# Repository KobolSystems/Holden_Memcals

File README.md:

# Holden Memcals

## **Project**: Drop-in Replacement Memcals for Delco '808 ECUs 

<!-- Repo Cover Image -->

<!-- Repo Stats -->

## Details
<p align="justify"> 
Holden Memcals is a repository dedicated to the development of replacement memcals for the VN-VT Commodore ECU. This repository serves as a comprehensive resource, storing all publicly available tunes for these memcals and offering detailed instructions on how to assemble and program existing tunes to them. Whether you are looking to enhance your vehicle's performance or simply maintain its functionality, Holden Memcals provides the necessary tools and information to support your endeavors.
</p>

<!-- To Do List -->
## Project To Do List
- [ ] Reverse engineer memcal
  - [ ] Analyze original memcal architecture
  - [ ] Identify key components and their functions
  - [ ] Document findings

- [ ] Design PCBs
  - [ ] Create schematics
  - [ ] Design PCB layout
  - [ ] Prototype and test PCB
  - [ ] Finalize design

- [ ] Sort tunes
  - [ ] Gather publicly available tunes
  - [ ] Categorize tunes based on vehicle model and specifications
  - [ ] Verify and validate tune files

- [ ] Upload tunes
  - [ ] Organize tunes into appropriate directories
  - [ ] Create metadata files for each tune (e.g., version, date, author)
  - [ ] Ensure tunes are correctly formatted and ready for use

- [ ] Write documentation
  - [ ] Develop detailed assembly instructions
  - [ ] Create programming guides for existing tunes
  - [ ] Write a troubleshooting guide
  - [ ] Document reverse engineering process
  - [ ] Update README with project overview and usage instructions

<!-- Licencing Always at the Bottom -->
## Licencing

This project is licensed under the Creative Commons Attribution-NonCommercial-ShareAlike 4.0 International License.

You are free to:

- **Share** — copy and redistribute the material in any medium or format
- **Adapt** — remix, transform, and build upon the material

Under the following terms:

- **Attribution** — You must give appropriate credit, provide a link to the license, and indicate if changes were made. You may do so in any reasonable manner, but not in any way that suggests the licensor endorses you or your use.
- **NonCommercial** — You may not use the material for commercial purposes.
- **ShareAlike** — If you remix, transform, or build upon the material, you must distribute your contributions under the same license as the original.

No additional restrictions — You may not apply legal terms or technological measures that legally restrict others from doing anything the license permits.

For more information, please visit [Creative Commons Attribution-NonCommercial-ShareAlike 4.0 International License](https://creativecommons.org/licenses/by-nc-sa/4.0/).

## Disclaimer
<p align="justify"> 
The tunes, BIN, ADX, and XDF files included in this repository are written by third parties (including Holden and other enthusiasts). These files may not be suitable for all applications. Kobol Systems makes no guarantee of their fitness for any particular purpose. Use of these files is entirely at your own risk. 
<br><br>
By using these files, you acknowledge that Kobol Systems is not responsible for any damage or issues that may arise from their use. Always ensure that any modifications to your vehicle's ECU are performed by a qualified professional and that you understand the potential risks involved.
</p>

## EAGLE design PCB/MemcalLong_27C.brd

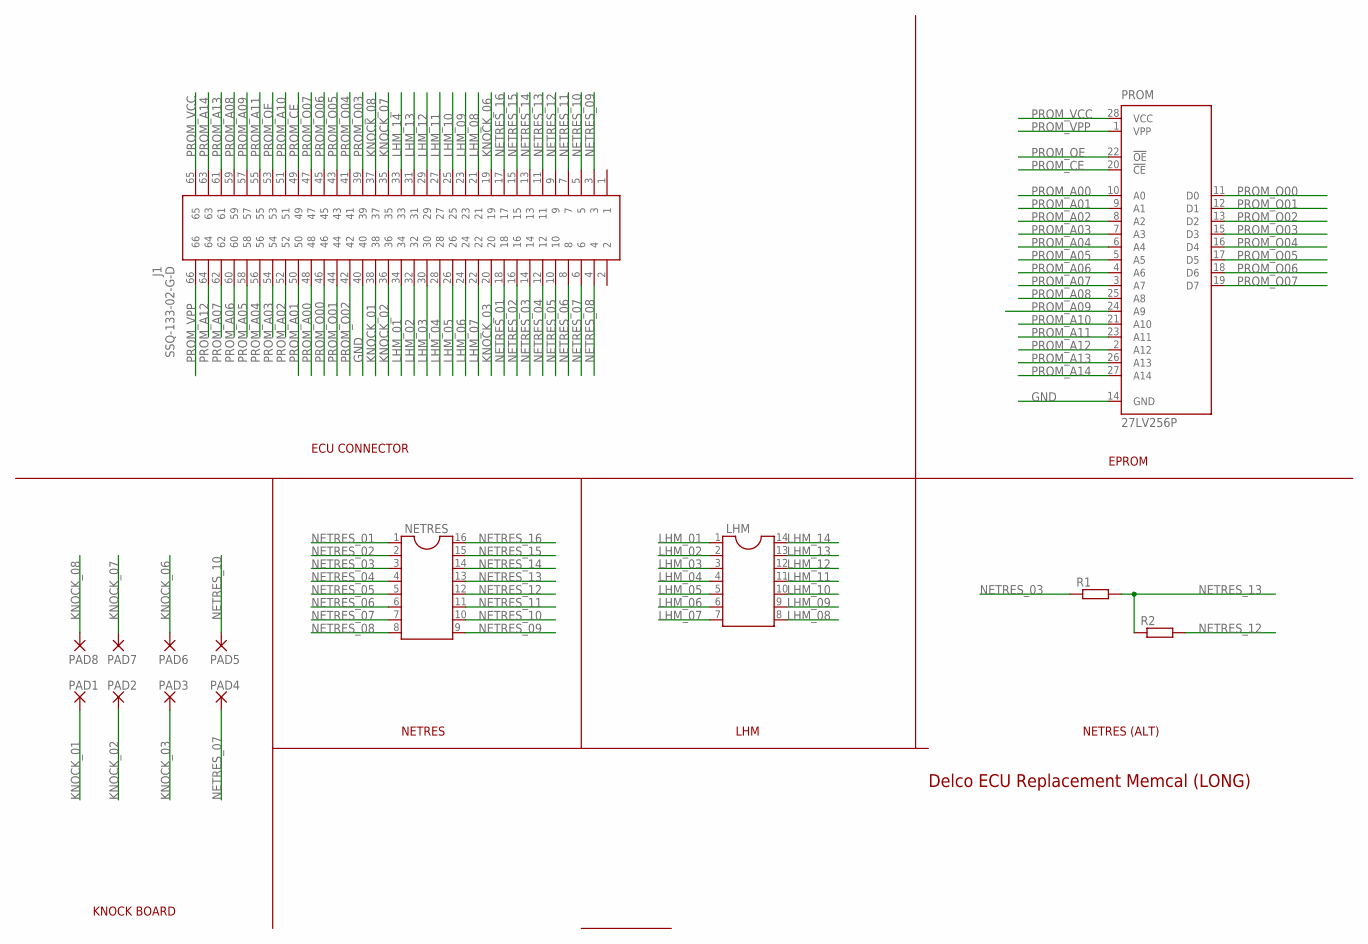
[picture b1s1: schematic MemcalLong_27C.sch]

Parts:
J1: SSQ-133-02-G-D; SSQ-133-XX-YYY
LHM: DIL14S; SOCKET-14
NETRES: DIL16S; SOCKET-16
PAD1, PAD2, PAD3, PAD4, PAD5, PAD6, PAD7, PAD8: SMD2; SMD1,27-2,54
PROM: 27LV256P; DIL28-6
R1, R2: R-EU_0204/7; 0204/7

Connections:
GND: J1.40, PROM.14 (GND)
KNOCK_01: J1.38, PAD1.1
KNOCK_02: J1.36, PAD2.1
KNOCK_03: J1.20, PAD3.1
KNOCK_06: J1.19, PAD6.1
KNOCK_07: J1.35, PAD7.1
KNOCK_08: J1.37, PAD8.1
LHM_01: J1.34, LHM.1
LHM_02: J1.32, LHM.2
LHM_03: J1.30, LHM.3
LHM_04: J1.28, LHM.4
LHM_05: J1.26, LHM.5
LHM_06: J1.24, LHM.6
LHM_07: J1.22, LHM.7
LHM_08: J1.21, LHM.8
LHM_09: J1.23, LHM.9
LHM_10: J1.25, LHM.10
LHM_11: J1.27, LHM.11
LHM_12: J1.29, LHM.12
LHM_13: J1.31, LHM.13
LHM_14: J1.33, LHM.14
NETRES_01: J1.18, NETRES.1
NETRES_02: J1.16, NETRES.2
NETRES_03: J1.14, NETRES.3, R1.1
NETRES_04: J1.12, NETRES.4
NETRES_05: J1.10, NETRES.5
NETRES_06: J1.8, NETRES.6
NETRES_07: J1.6, NETRES.7, PAD4.1
NETRES_08: J1.4, NETRES.8
NETRES_09: J1.3, NETRES.9
NETRES_10: J1.5, NETRES.10, PAD5.1
NETRES_11: J1.7, NETRES.11
NETRES_12: J1.9, NETRES.12, R2.2
NETRES_13: J1.11, NETRES.13, R1.2, R2.1
NETRES_14: J1.13, NETRES.14
NETRES_15: J1.15, NETRES.15
NETRES_16: J1.17, NETRES.16
PROM_A00: J1.48, PROM.10 (A0)
PROM_A01: J1.50, PROM.9 (A1)
PROM_A02: J1.52, PROM.8 (A2)
PROM_A03: J1.54, PROM.7 (A3)
PROM_A04: J1.56, PROM.6 (A4)
PROM_A05: J1.58, PROM.5 (A5)
PROM_A06: J1.60, PROM.4 (A6)
PROM_A07: J1.62, PROM.3 (A7)
PROM_A08: J1.59, PROM.25 (A8)
PROM_A09: J1.57, PROM.24 (A9)
PROM_A10: J1.51, PROM.21 (A10)
PROM_A11: J1.55, PROM.23 (A11)
PROM_A12: J1.64, PROM.2 (A12)
PROM_A13: J1.61, PROM.26 (A13)
PROM_A14: J1.63, PROM.27 (A14)
PROM_CE: J1.49, PROM.20 (!CE)
PROM_O00: J1.46, PROM.11 (D0)
PROM_O01: J1.44, PROM.12 (D1)
PROM_O02: J1.42, PROM.13 (D2)
PROM_O03: J1.39, PROM.15 (D3)
PROM_O04: J1.41, PROM.16 (D4)
PROM_O05: J1.43, PROM.17 (D5)
PROM_O06: J1.45, PROM.18 (D6)
PROM_O07: J1.47, PROM.19 (D7)
PROM_OE: J1.53, PROM.22 (!OE)
PROM_VCC: J1.65, PROM.28 (VCC)
PROM_VPP: J1.66, PROM.1 (VPP)

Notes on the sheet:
Delco ECU Replacement Memcal (LONG)
EPROM
ECU CONNECTOR
NETRES
LHM
KNOCK BOARD
NETRES (ALT)

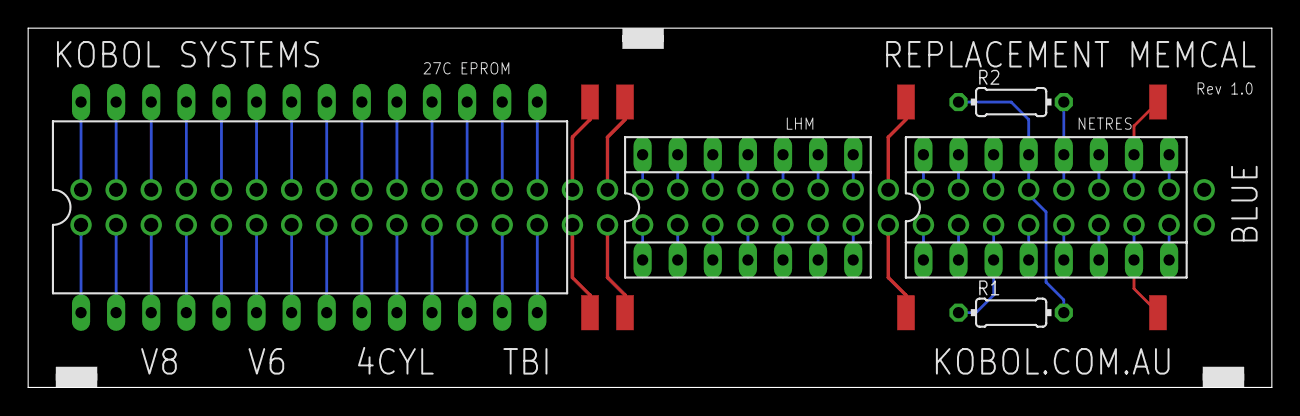
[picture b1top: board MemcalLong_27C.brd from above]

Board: 2 copper layers, 90.0 x 26.0 mm, 14 parts (1 on the bottom side), 64 nets.

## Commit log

2024-08-02 Partial Bin Upload
2024-08-04 doc updates
2025-05-24 MemcalLong and Updates
